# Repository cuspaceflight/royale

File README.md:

<p align="center">
	
	<h1 align="center">PROJECT ROYALE</h1>
	<h3 align="center">Cambridge University Spaceflight</h3>
</p>

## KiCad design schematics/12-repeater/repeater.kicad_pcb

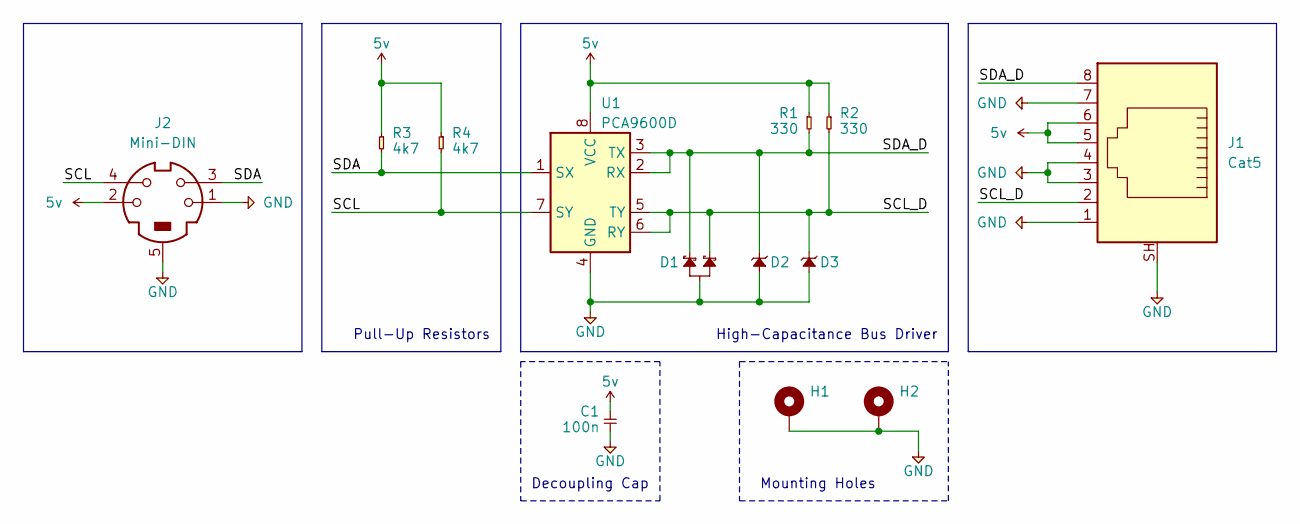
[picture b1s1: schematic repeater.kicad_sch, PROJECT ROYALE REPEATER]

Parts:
C1: 100n; C_0805_2012Metric; Farnell 9406387
D1: BAT54A; SOT-23; Farnell 2675345
D2, D3: Diode_Zener_BZX84-C15; SOT-23; Farnell 2319204
H1, H2: MountingHole_Pad; MountingHole_3.2mm_M3_Pad_Via
J1: Cat5; RJ45_Amphenol_RJHSE5380; Farnell 1849916
J2: Mini-DIN; TE_5749181-1; Farnell 3791398
R1, R2: 330; R_0805_2012Metric; Farnell 9333037
R3, R4: 4k7; R_0805_2012Metric; Farnell 2447672
U1: PCA9600D; SO-8_3.9x4.9mm_P1.27mm; Farnell 2775968

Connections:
5v: C1.1, J1.5, J1.6, J2.2, R1.1, R2.1, R3.1, R4.1, U1.8 (VCC)
/SCL: J2.4, R4.2, U1.7 (SY)
/SCL_D: D1.2, D3.3 (K), J1.2, R2.2, U1.5 (TY), U1.6 (RY)
/SDA: J2.3, R3.2, U1.1 (SX)
/SDA_D: D1.1, D2.3 (K), J1.8, R1.2, U1.2 (RX), U1.3 (TX)
GND: C1.2, D1.3, D2.1 (A), D3.1 (A), H1.1, H2.1, J1.1, J1.3, J1.4, J1.7, J1.SH, J2.1, J2.5, U1.4 (GND)

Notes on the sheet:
Decoupling Cap
Pull-Up Resistors
Mounting Holes
High-Capacitance Bus Driver

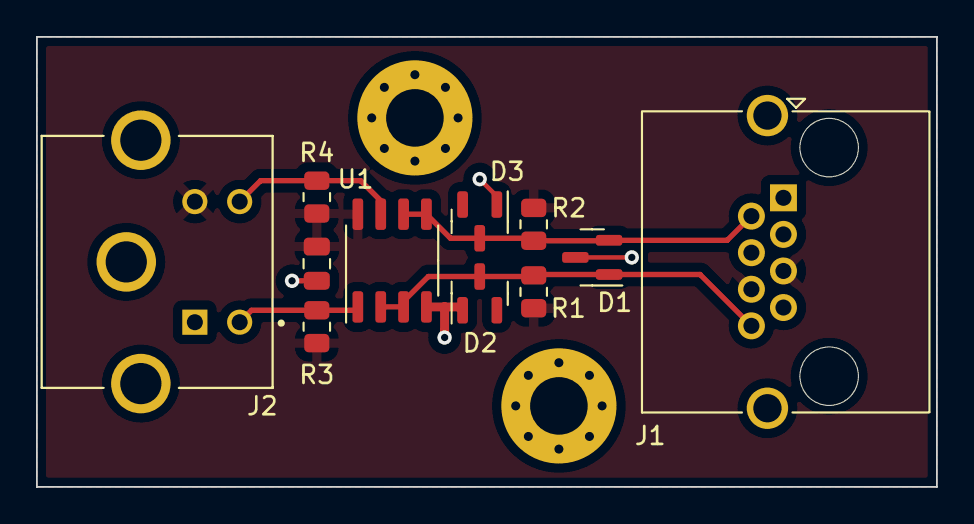
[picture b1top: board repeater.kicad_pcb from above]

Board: 4 copper layers, 50.0 x 25.0 mm, 13 parts (0 on the bottom side), 6 nets.

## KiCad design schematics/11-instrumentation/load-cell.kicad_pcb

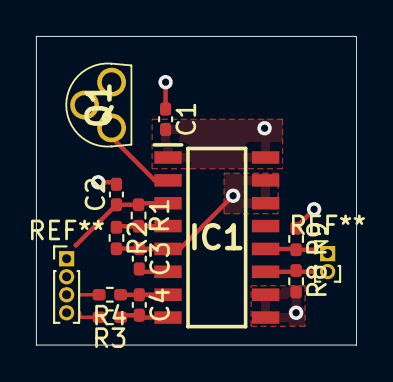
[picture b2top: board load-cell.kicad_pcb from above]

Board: 4 copper layers, 17.8 x 17.1 mm, 12 parts (0 on the bottom side), 9 nets.

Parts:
C1: 10u; C_0402_1005Metric_Pad0.74x0.62mm_HandSolder
C2: 100u; C_0402_1005Metric_Pad0.74x0.62mm_HandSolder
C3, C4: 0.1u; C_0402_1005Metric_Pad0.74x0.62mm_HandSolder
IC1: HX711; SOIC127P600X160-16N
Q1: S8550; MJE13001TP
R1, R2: 1k; R_0402_1005Metric_Pad0.72x0.64mm_HandSolder
R3, R4: 100; R_0402_1005Metric_Pad0.72x0.64mm_HandSolder
R8, R9: 4k7; R_0402_1005Metric_Pad0.72x0.64mm_HandSolder

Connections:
1v8: C1.2, C2.1, IC1.1 (VSUP), IC1.3 (AVDD), IC1.16 (DVDD), Q1.2 (C), Q1.3 (E), R1.1, R9.1
/DT: IC1.12 (DOUT), R9.2
/SCK: IC1.11 (PD_SCK), R8.1
GND: C1.1, C2.2, C3.1, IC1.5 (AGND), IC1.9 (INNB), IC1.10 (INPB), IC1.14 (XI), IC1.15 (RATE), R2.2, R8.2
unnamed: C3.2, IC1.6 (VBG)
unnamed: C4.1, IC1.7 (INNA), R4.1
unnamed: C4.2, IC1.8 (INPA), R3.1
unnamed: IC1.2 (BASE), Q1.1 (B)
unnamed: IC1.4 (VFB), R1.2, R2.1

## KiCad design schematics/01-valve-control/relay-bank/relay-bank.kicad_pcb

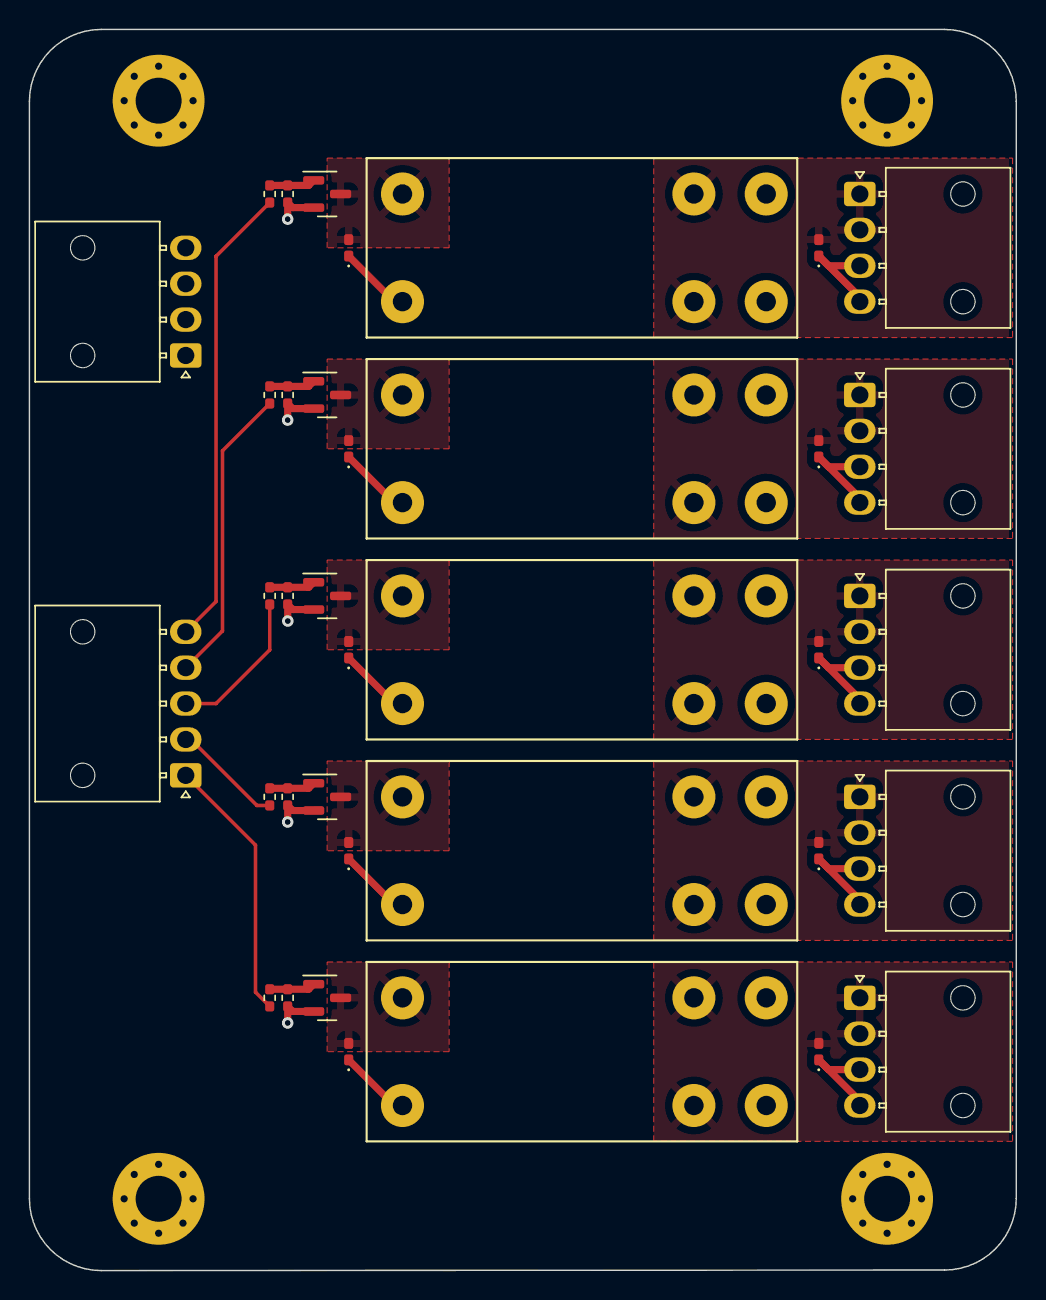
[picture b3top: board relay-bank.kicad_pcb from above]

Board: 4 copper layers, 68.8 x 86.5 mm, 41 parts (0 on the bottom side), 22 nets.

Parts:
D201, D301, D401, D501, D601: Diode_ESD; D_0402
D202, D302, D402, D502, D602: Diode_Schottky; D_0402
H101, H102, H103, H104: MountingHole_Pad
J102: PWR; Molex_Nano-Fit_105313-xx04_1x04_P2.50mm_Horizontal
J103: EN; Molex_Nano-Fit_105313-xx05_1x05_P2.50mm_Horizontal
J201, J301, J401, J501, J601: VALVE; Molex_Nano-Fit_105313-xx04_1x04_P2.50mm_Horizontal
K201, K301, K401, K501, K601: SPST Relay; Relay
Q201, Q301, Q401, Q501, Q601: BSS138
R201, R301, R401, R501, R601: 100; R_0402
R202, R302, R402, R502, R602: 110k; R_0402

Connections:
/EN_01: J103.1, R201.1
/EN_02: J103.2, R301.1
/EN_03: J103.3, R401.1
/EN_04: J103.4, R501.1
/EN_05: J103.5, R601.1
GND: D201.1, D301.1, D401.1, D501.1, D601.1, H101.1, H102.1, H103.1, H104.1, J102.3, J102.4, J201.3, J201.4, J301.3, J301.4, J401.3, J401.4, J501.3, J501.4, J601.3, J601.4, Q201.2 (S), Q301.2 (S), Q401.2 (S), Q501.2 (S), Q601.2 (S), R202.2, R302.2, R402.2, R502.2, R602.2
unnamed: D201.2, J201.1, J201.2, K201.3
unnamed: D202.2, K201.1, Q201.3 (D)
unnamed: D301.2, J301.1, J301.2, K301.3
unnamed: D302.2, K301.1, Q301.3 (D)
unnamed: D401.2, J401.1, J401.2, K401.3
unnamed: D402.2, K401.1, Q401.3 (D)
unnamed: D501.2, J501.1, J501.2, K501.3
unnamed: D502.2, K501.1, Q501.3 (D)
unnamed: D601.2, J601.1, J601.2, K601.3
unnamed: D602.2, K601.1, Q601.3 (D)
unnamed: Q201.1 (G), R201.2, R202.1
unnamed: Q301.1 (G), R301.2, R302.1
unnamed: Q401.1 (G), R401.2, R402.1
unnamed: Q501.1 (G), R501.2, R502.1
unnamed: Q601.1 (G), R601.2, R602.1
PWR: D202.1, D302.1, D402.1, D502.1, D602.1, J102.1, J102.2, K201.2, K201.4, K301.2, K301.4, K401.2, K401.4, K501.2, K501.4, K601.2, K601.4

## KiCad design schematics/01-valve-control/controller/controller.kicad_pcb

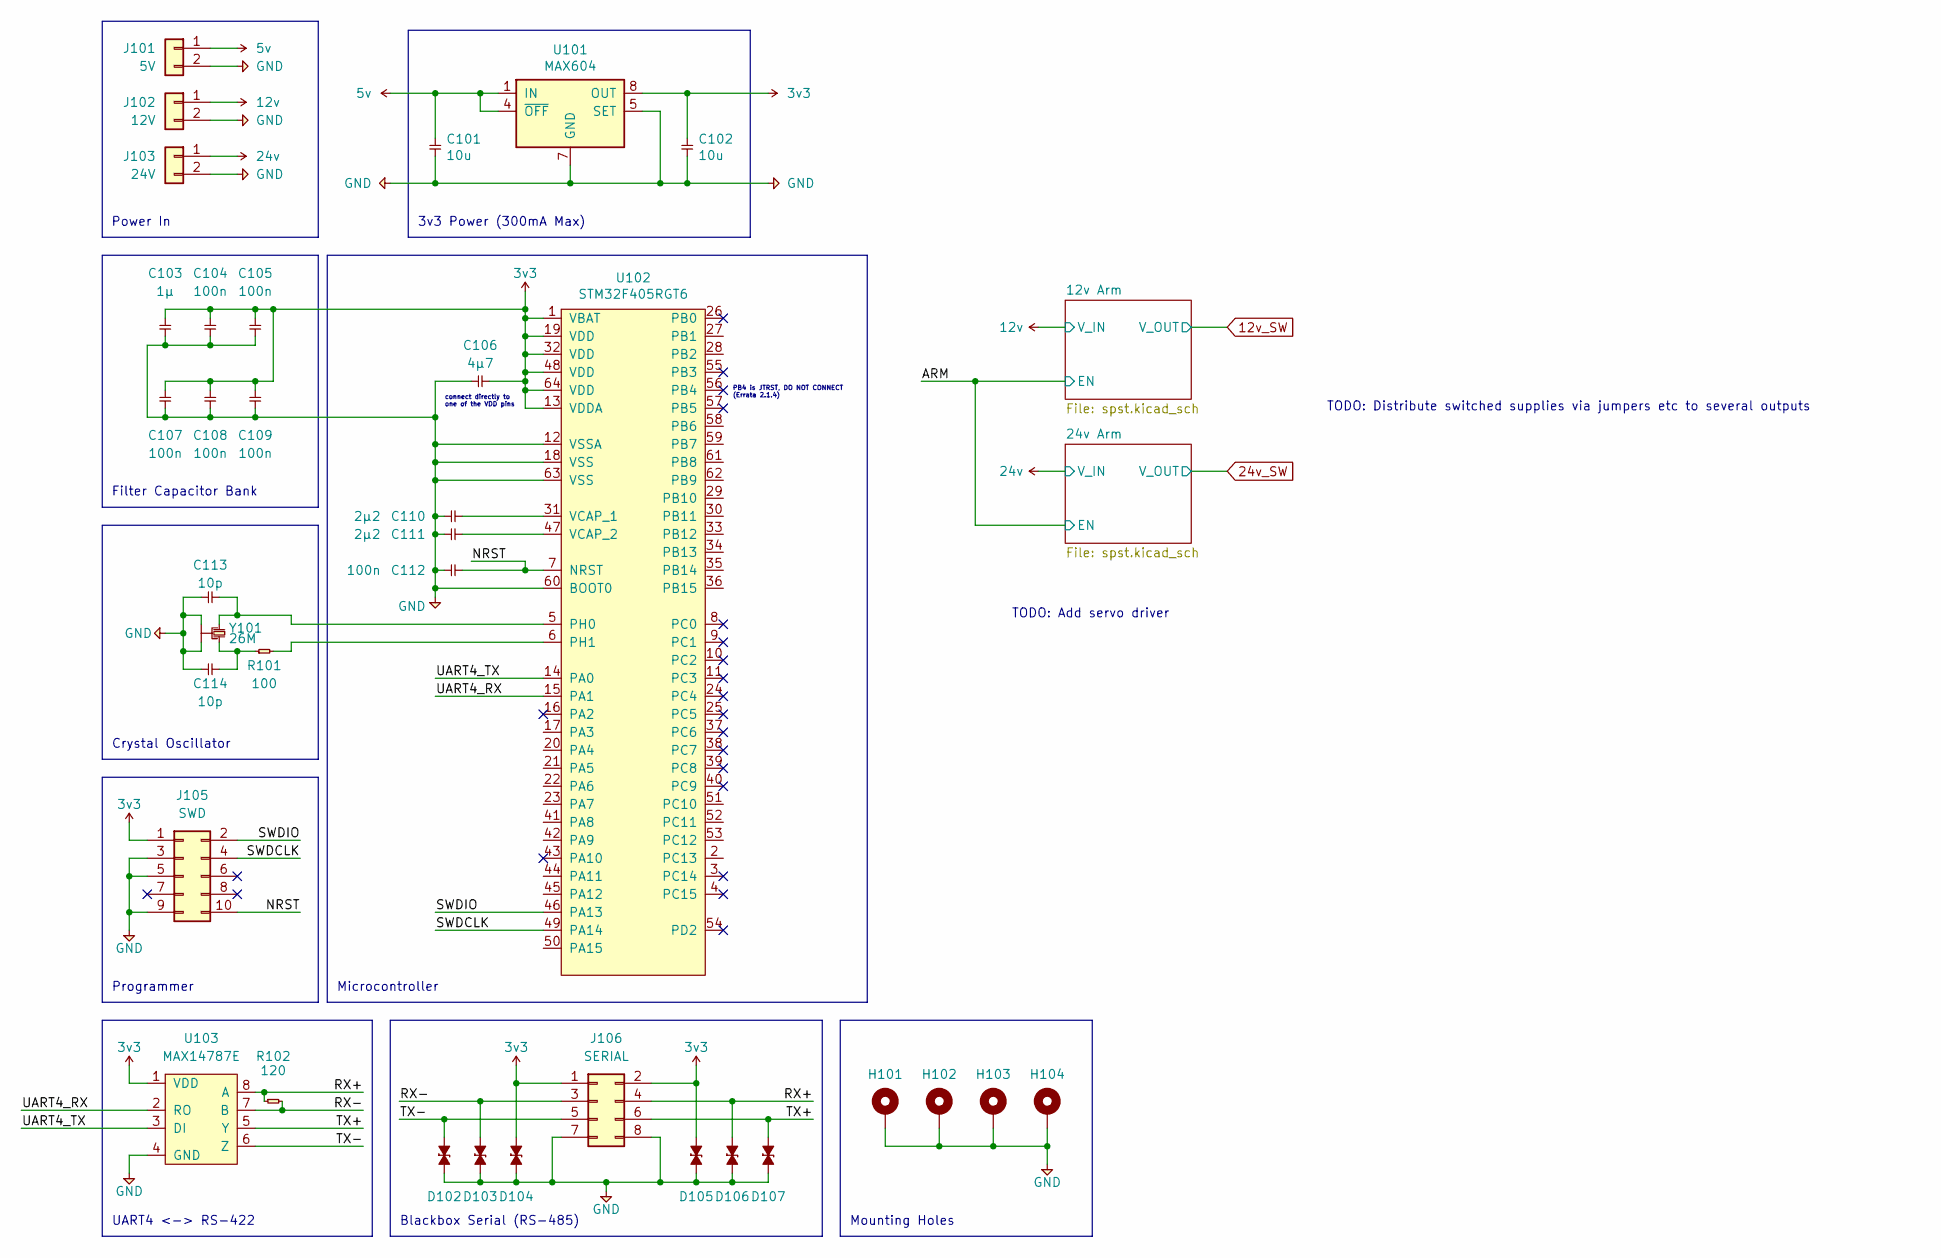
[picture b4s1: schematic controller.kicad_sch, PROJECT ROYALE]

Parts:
C101, C102: 10u; C_0402
C103: 1µ; C_0402; Farnell 2496814
C104, C105, C107, C108, C109, C112: 100n; C_0402; Farnell 2496771
C106: 4µ7; C_0402; Farnell 2426952
C110, C111: 2µ2; C_0402; Farnell 2362088
C113, C114: 10p; C_0402
D102, D103, D104, D105, D106, D107: Diode_ESD; D_0402; Farnell 2368169
H101, H102, H103, H104: MountingHole_Pad
J101: 5V
J102: 12V
J103: 24V
J105: SWD; Header_SWD
J106: SERIAL; RJ45_Amphenol_RJHSE5380
R101: 100; R_0402
R102: 120; R_0402
U101: MAX604
U102: STM32F405RGT6; Farnell 2064363
U103: MAX14787E; Farnell 2528531
Y101: 26M; Xtal_SMD_2016; Farnell 2506952

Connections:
1v8: C101.1, J101.1, U101.1 (IN), U101.4 (~OFF)
3v3: C102.1, C103.2, C104.2, C105.2, C106.2, C107.2, C108.2, C109.2, D104.2, D105.2, J105.1, J106.1, J106.2, U101.8 (OUT), U102.1 (VBAT), U102.13 (VDDA), U102.19 (VDD), U102.32 (VDD), U102.48 (VDD), U102.64 (VDD), U103.1 (VDD); also elsewhere on the board
/NRST: C112.2, J105.10, U102.7 (NRST)
/RX+: D106.2, J106.4, R102.1, U103.8 (A)
/RX-: D103.2, J106.3, R102.2, U103.7 (B)
/SWDCLK: J105.4, U102.49 (PA14)
/SWDIO: J105.2, U102.46 (PA13)
/TX+: D107.2, J106.6, U103.5 (Y)
/TX-: D102.2, J106.5, U103.6 (Z)
/UART4_RX: U102.15 (PA1), U103.2 (RO)
/UART4_TX: U102.14 (PA0), U103.3 (DI)
GND: C101.2, C102.2, C103.1, C104.1, C105.1, C106.1, C107.1, C108.1, C109.1, C110.1, C111.1, C112.1, C113.1, C114.1, D102.1, D103.1, D104.1, D105.1, D106.1, D107.1, H101.1, H102.1, H103.1, H104.1, J101.2, J102.2, J103.2, J105.3, J105.5, J105.9, J106.7, J106.8, U101.2 (GND), U101.3 (GND), U101.5 (SET), U101.6 (GND), U101.7 (GND), U102.12 (VSSA), U102.18 (VSS), U102.60 (BOOT0), U102.63 (VSS), U103.4 (GND), Y101.2, Y101.4; also elsewhere on the board
unnamed: C110.2, U102.31 (VCAP_1)
unnamed: C111.2, U102.47 (VCAP_2)
unnamed: C113.2, U102.5 (PH0), Y101.1
unnamed: C114.2, R101.1, Y101.3
unnamed: R101.2, U102.6 (PH1)

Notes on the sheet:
Microcontroller
UART4 <-> RS-422
Power In
Mounting Holes
PB4 is JTRST, DO NOT CONNECT (Errata 2.1.4)
TODO: Add servo driver
Filter Capacitor Bank
Crystal Oscillator
TODO: Distribute switched supplies via jumpers etc to several outputs
Programmer
Blackbox Serial (RS-485)
connect directly to one of the VDD pins
3v3 Power (300mA Max)

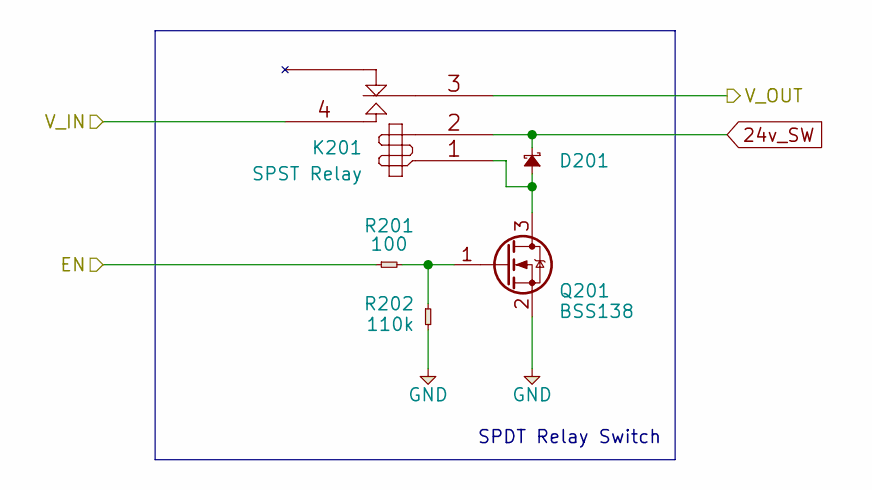
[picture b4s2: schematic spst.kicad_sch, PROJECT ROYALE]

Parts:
D201: Diode_Schottky; D_0402
K201: SPST Relay; Relay
Q201: BSS138
R201: 100; R_0402
R202: 110k; R_0402

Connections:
3v3: K201.4; also elsewhere on the board
12v_SW: K201.3
24v_SW: D201.1, K201.2; also elsewhere on the board
/ARM: R201.1; also elsewhere on the board
GND: Q201.2 (S), R202.2; also elsewhere on the board
unnamed: D201.2, K201.1, Q201.3 (D)
unnamed: Q201.1 (G), R201.2, R202.1

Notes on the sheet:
SPDT Relay Switch

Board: 2 copper layers, 42 parts (0 on the bottom side), 23 nets, no tracks yet.

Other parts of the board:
D301: Diode_Schottky; D_0402
K301: SPST Relay; Relay
Q301: BSS138
R301: 100; R_0402
R302: 110k; R_0402

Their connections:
3v3: K301.4; also elsewhere on the board
24v_SW: D301.1, K301.2, K301.3; also elsewhere on the board
/ARM: R301.1; also elsewhere on the board
GND: Q301.2 (S), R302.2; also elsewhere on the board
unnamed: D301.2, K301.1, Q301.3 (D)
unnamed: Q301.1 (G), R301.2, R302.1

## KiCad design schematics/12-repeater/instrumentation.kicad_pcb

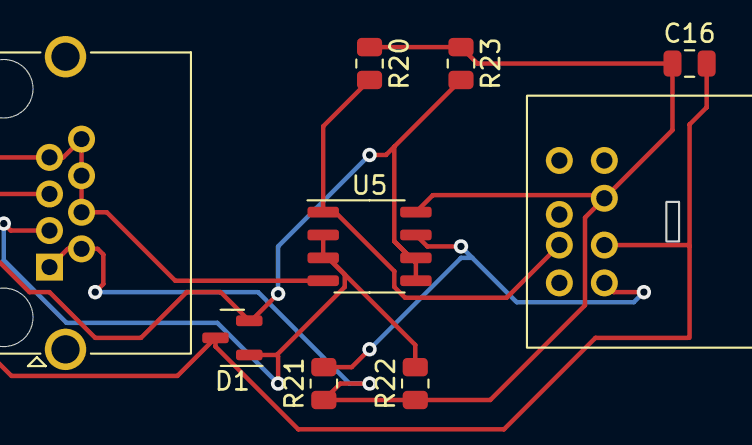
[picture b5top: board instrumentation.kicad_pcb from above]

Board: 2 copper layers, 9 parts (0 on the bottom side), 6 nets.

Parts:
C16: 100n; C_0805_2012Metric
D1: BAT54A; SOT-23
J4: RJHSE-5380; RJ45_Amphenol_RJHSE5380
J12: PSG01571; Mini-Din-Through-Hole
R20, R21: 4k7; R_0805_2012Metric
R22, R23: 1k; R_0805_2012Metric
U5: PCA9600D; SO-8_3.9x4.9mm_P1.27mm

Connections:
3v3: C16.1, J4.1, J4.2, J12.2, R20.1, R21.1, R22.1, R23.1, U5.8 (VCC)
/HS_SCL: J12.3, R21.2, U5.7 (SY)
/HS_SDA: J12.4, R20.2, U5.1 (SX)
GND: C16.2, D1.3, J4.4, J4.6, J4.7, J4.8, J12.1, U5.4 (GND)
unnamed: D1.1, J4.3, R22.2, U5.2 (RX), U5.3 (TX)
unnamed: D1.2, J4.5, R23.2, U5.5 (TY), U5.6 (RY)

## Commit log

2021-08-15 Add README
2021-11-02 Add preliminary schematics
2021-12-02 Update valve controller schematic to match new system architecture
2021-12-02 Fix libs
2022-01-09 Migrate instrumentation to KiCad 6
2022-01-12 Break valve controller into separate boards
2022-01-12 Add connector for valve control enable inputs
2022-01-12 Remove silkscreen label on enable input connector
2022-01-26 Relay bank changes for manufacture
2022-01-26 Flatten directory structure
2022-01-30 Added mini-din connector
2022-01-30 added minidin
2022-01-31 Added footprint for the diode
2022-02-06 Added servo controller
2022-02-06 Added footprints minus din
2022-02-06 Added mini Din
2022-02-06 Added stuff
2022-02-06 Added basic pcb
2022-02-06 moved to repeater folder
2022-02-08 Move schematics to correct folders
2022-02-08 Clean up extraneous files
2022-02-08 Revert instrumentation to master
2022-02-08 Clean up schematic and re-wire RJ45 connector
2022-02-13 load cell
2022-02-13 Preliminary board layout
2022-02-13 load cell schematic
2022-02-13 added BZX84-C15 diodes, 1.8v not fixed
2022-02-20 added mounting holes
2022-02-27 Removed driver mosfets
2022-02-27 Refined repeater pcb
2022-03-04 load cell pcb edited
2022-03-06 Update repeater ready for manufacture
2022-03-06 Update RJ-45 footprint and link model
2022-03-06 Replace mini-DIN with more well-documented part
2022-03-06 Minor cleanup to accomodate new connector
2022-03-06 Fix minor symbol errors
2022-03-07 Reorder RJ45 pins to simplify board layout
2022-03-07 What if it was purple?
2022-03-07 Add silkscreen
2022-03-07 Silkscreen tweaks for manufacture
2022-03-17 DC output switching, GPIO expander
2022-03-17 added files
